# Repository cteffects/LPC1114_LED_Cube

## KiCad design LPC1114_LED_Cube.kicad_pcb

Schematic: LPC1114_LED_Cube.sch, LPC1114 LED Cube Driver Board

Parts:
AUX_I/O_0: Conn_02x08_Odd_Even; Multicomp_MC9A12-1634_2x08x2.54mm_Straight
C101, C110, C111, C114: 10uf; CP_Radial_D5.0mm_P2.50mm
C102, C104, C108, C109, C112, C113: 0.1uf; C_1206_HandSoldering
C103, C105: 22pf; C_1206_HandSoldering
C106, C107: 39pf; C_1206_HandSoldering
CH340T_0: CH340T; SSOP-20_5.3x7.2mm_Pitch0.65mm
CH340_CKO_0: Conn_01x01; Pin_Header_Straight_1x01_Pitch2.54mm
LAYER_VOUT0: Conn_01x08; Pin_Header_Straight_1x08_Pitch2.54mm
LD33V_0: LD33V; TO-220-3_Horizontal
LED_CH0, LED_CH1, LED_CH2, LED_CH3: Conn_02x08_Odd_Even; Multicomp_MC9A12-1634_2x08x2.54mm_Straight
LED_CH0_CTRL0, LED_CH1_CTRL0, LED_CH2_CTRL0, LED_CH3_CTRL0: TLC5940PWPR; TSSOP-28-1EP_4.4x9.7mm_Pitch0.65mm; MPN TLC5940PWPR; Digi-Key_PN 296-35975-1-ND
LPC1114_0: LPC1114FBD48-302; LQFP-48_7x7mm_Pitch0.5mm
MODE_SELECT_0: SW_DIP_x02; SW_DIP_x2_W7.62mm_Slide
PWR_JACK0: Barrel_Jack; BARREL_JACK
PWR_SEL1: Conn_01x03; Pin_Header_Straight_1x03_Pitch2.54mm
R101, R102, R103, R104: R; R_1206_HandSoldering
RESET0: SW_SPST; SW_Tactile_Straight_KSA0Axx1LFTR
SWDEBUG0: Conn_02x05_Odd_Even; Pin_Header_Straight_2x05_Pitch1.27mm
USB_CONN_0: USB_B
Wireless/SPI_1: Conn_02x04_Odd_Even; Pin_Header_Straight_2x04_Pitch2.54mm
XERR_CH0_BRIDGE0, XERR_CH0_BRIDGE1, XERR_CH1_BRIDGE0, XERR_CH1_BRIDGE1, XERR_CH2_BRIDGE0, XERR_CH2_BRIDGE1: Conn_01x01; Pin_Header_Straight_1x01_Pitch2.54mm
XERR_CH3_BRIDGE0: Conn_01x02; Pin_Header_Straight_1x02_Pitch2.54mm
Y101, Y102: 12MHZ; Crystal_HC49-U_Vertical

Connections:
/LayerController/LAYER_0_PWR: LAYER_VOUT0.1; also elsewhere on the board
/LayerController/LAYER_1_PWR: LAYER_VOUT0.2; also elsewhere on the board
/LayerController/LAYER_2_PWR: LAYER_VOUT0.3; also elsewhere on the board
/LayerController/LAYER_3_PWR: LAYER_VOUT0.4; also elsewhere on the board
/LayerController/LAYER_4_PWR: LAYER_VOUT0.5; also elsewhere on the board
/LayerController/LAYER_5_PWR: LAYER_VOUT0.6; also elsewhere on the board
/LayerController/LAYER_6_PWR: LAYER_VOUT0.7; also elsewhere on the board
/LayerController/LAYER_7_PWR: LAYER_VOUT0.8; also elsewhere on the board
AUX_SPI_MISO: LPC1114_0.26 (PIO2_2), Wireless/SPI_1.7
AUX_SPI_MOSI: LPC1114_0.38 (PIO2_3), Wireless/SPI_1.6
AUX_SPI_SCK: LPC1114_0.31 (PIO2_11), Wireless/SPI_1.5
AUX_SPI_SSEL: LPC1114_0.2 (PIO2_0), Wireless/SPI_1.3
BLANK: LED_CH0_CTRL0.2 (Blank), LED_CH1_CTRL0.2 (Blank), LED_CH2_CTRL0.2 (Blank), LED_CH3_CTRL0.2 (Blank), LPC1114_0.34 (PIO1_1)
DCPRG: LED_CH0_CTRL0.26 (DCPRG), LED_CH1_CTRL0.26 (DCPRG), LED_CH2_CTRL0.26 (DCPRG), LED_CH3_CTRL0.26 (DCPRG), LPC1114_0.40 (PIO1_4)
GND: AUX_I/O_0.13, AUX_I/O_0.15, AUX_I/O_0.16, C101.2, C102.2, C103.2, C104.2, C105.2, C106.2, C107.2, C108.2, C109.2, C110.2, C111.2, C112.2, C113.2, C114.2, CH340T_0.8, LD33V_0.1, LED_CH0_CTRL0.1 (GND), LED_CH0_CTRL0.29, LED_CH1_CTRL0.1 (GND), LED_CH1_CTRL0.29, LED_CH2_CTRL0.1 (GND), LED_CH2_CTRL0.29, LED_CH3_CTRL0.1 (GND), LED_CH3_CTRL0.29, LPC1114_0.5 (VSS), LPC1114_0.41 (VSS), MODE_SELECT_0.3, MODE_SELECT_0.4, PWR_JACK0.2, R101.1, R102.1, R103.1, R104.1, RESET0.2, SWDEBUG0.3, SWDEBUG0.5, SWDEBUG0.9, USB_CONN_0.4, USB_CONN_0.5, Wireless/SPI_1.1; also elsewhere on the board
INPUT_MODE_SELECT: AUX_I/O_0.5, LPC1114_0.10 (PIO0_2), MODE_SELECT_0.2
ISP_ENTRY: LPC1114_0.4 (PIO0_1), MODE_SELECT_0.1
LAYER_0_ON: LPC1114_0.19 (PIO2_4); also elsewhere on the board
LAYER_1_ON: LPC1114_0.20 (PIO2_5); also elsewhere on the board
LAYER_2_ON: LPC1114_0.1 (PIO2_6); also elsewhere on the board
LAYER_3_ON: LPC1114_0.11 (PIO2_7); also elsewhere on the board
LAYER_4_ON: LPC1114_0.12 (PIO2_8); also elsewhere on the board
LAYER_5_ON: LPC1114_0.24 (PIO2_9); also elsewhere on the board
LAYER_6_ON: LPC1114_0.25 (PIO2_10); also elsewhere on the board
LAYER_7_ON: LPC1114_0.13 (PIO2_1); also elsewhere on the board
LED_CH0_0: LED_CH0.15, LED_CH0_CTRL0.7 (OUT0)
LED_CH0_1: LED_CH0.13, LED_CH0_CTRL0.8 (OUT1)
LED_CH0_2: LED_CH0.11, LED_CH0_CTRL0.9 (OUT2)
LED_CH0_3: LED_CH0.9, LED_CH0_CTRL0.10 (OUT3)
LED_CH0_4: LED_CH0.7, LED_CH0_CTRL0.11 (OUT4)
LED_CH0_5: LED_CH0.5, LED_CH0_CTRL0.12 (OUT5)
LED_CH0_6: LED_CH0.3, LED_CH0_CTRL0.13 (OUT6)
LED_CH0_7: LED_CH0.1, LED_CH0_CTRL0.14 (OUT7)
LED_CH0_8: LED_CH0.2, LED_CH0_CTRL0.15 (OUT8)
LED_CH0_9: LED_CH0.4, LED_CH0_CTRL0.16 (OUT9)
LED_CH0_10: LED_CH0.6, LED_CH0_CTRL0.17 (OUT10)
LED_CH0_11: LED_CH0.8, LED_CH0_CTRL0.18 (OUT11)
LED_CH0_12: LED_CH0.10, LED_CH0_CTRL0.19 (OUT12)
LED_CH0_13: LED_CH0.12, LED_CH0_CTRL0.20 (OUT13)
LED_CH0_14: LED_CH0.14, LED_CH0_CTRL0.21 (OUT14)
LED_CH0_15: LED_CH0.16, LED_CH0_CTRL0.22 (OUT15)
LED_CH1_0: LED_CH1.15, LED_CH1_CTRL0.7 (OUT0)
LED_CH1_1: LED_CH1.13, LED_CH1_CTRL0.8 (OUT1)
LED_CH1_2: LED_CH1.11, LED_CH1_CTRL0.9 (OUT2)
LED_CH1_3: LED_CH1.9, LED_CH1_CTRL0.10 (OUT3)
LED_CH1_4: LED_CH1.7, LED_CH1_CTRL0.11 (OUT4)
LED_CH1_5: LED_CH1.5, LED_CH1_CTRL0.12 (OUT5)
LED_CH1_6: LED_CH1.3, LED_CH1_CTRL0.13 (OUT6)
LED_CH1_7: LED_CH1.1, LED_CH1_CTRL0.14 (OUT7)
LED_CH1_8: LED_CH1.2, LED_CH1_CTRL0.15 (OUT8)
LED_CH1_9: LED_CH1.4, LED_CH1_CTRL0.16 (OUT9)
LED_CH1_10: LED_CH1.6, LED_CH1_CTRL0.17 (OUT10)
LED_CH1_11: LED_CH1.8, LED_CH1_CTRL0.18 (OUT11)
LED_CH1_12: LED_CH1.10, LED_CH1_CTRL0.19 (OUT12)
LED_CH1_13: LED_CH1.12, LED_CH1_CTRL0.20 (OUT13)
LED_CH1_14: LED_CH1.14, LED_CH1_CTRL0.21 (OUT14)
LED_CH1_15: LED_CH1.16, LED_CH1_CTRL0.22 (OUT15)
LED_CH2_0: LED_CH2.15, LED_CH2_CTRL0.7 (OUT0)
LED_CH2_1: LED_CH2.13, LED_CH2_CTRL0.8 (OUT1)
LED_CH2_2: LED_CH2.11, LED_CH2_CTRL0.9 (OUT2)
LED_CH2_3: LED_CH2.9, LED_CH2_CTRL0.10 (OUT3)
LED_CH2_4: LED_CH2.7, LED_CH2_CTRL0.11 (OUT4)
LED_CH2_5: LED_CH2.5, LED_CH2_CTRL0.12 (OUT5)
LED_CH2_6: LED_CH2.3, LED_CH2_CTRL0.13 (OUT6)
LED_CH2_7: LED_CH2.1, LED_CH2_CTRL0.14 (OUT7)
LED_CH2_8: LED_CH2.2, LED_CH2_CTRL0.15 (OUT8)
LED_CH2_9: LED_CH2.4, LED_CH2_CTRL0.16 (OUT9)
LED_CH2_10: LED_CH2.6, LED_CH2_CTRL0.17 (OUT10)
LED_CH2_11: LED_CH2.8, LED_CH2_CTRL0.18 (OUT11)
LED_CH2_12: LED_CH2.10, LED_CH2_CTRL0.19 (OUT12)
LED_CH2_13: LED_CH2.12, LED_CH2_CTRL0.20 (OUT13)
LED_CH2_14: LED_CH2.14, LED_CH2_CTRL0.21 (OUT14)
LED_CH2_15: LED_CH2.16, LED_CH2_CTRL0.22 (OUT15)
LED_CH3_0: LED_CH3.15, LED_CH3_CTRL0.7 (OUT0)
LED_CH3_1: LED_CH3.13, LED_CH3_CTRL0.8 (OUT1)
LED_CH3_2: LED_CH3.11, LED_CH3_CTRL0.9 (OUT2)
LED_CH3_3: LED_CH3.9, LED_CH3_CTRL0.10 (OUT3)
LED_CH3_4: LED_CH3.7, LED_CH3_CTRL0.11 (OUT4)
LED_CH3_5: LED_CH3.5, LED_CH3_CTRL0.12 (OUT5)
LED_CH3_6: LED_CH3.3, LED_CH3_CTRL0.13 (OUT6)
LED_CH3_7: LED_CH3.1, LED_CH3_CTRL0.14 (OUT7)
LED_CH3_8: LED_CH3.2, LED_CH3_CTRL0.15 (OUT8)
LED_CH3_9: LED_CH3.4, LED_CH3_CTRL0.16 (OUT9)
LED_CH3_10: LED_CH3.6, LED_CH3_CTRL0.17 (OUT10)
LED_CH3_11: LED_CH3.8, LED_CH3_CTRL0.18 (OUT11)
LED_CH3_12: LED_CH3.10, LED_CH3_CTRL0.19 (OUT12)
LED_CH3_13: LED_CH3.12, LED_CH3_CTRL0.20 (OUT13)
LED_CH3_14: LED_CH3.14, LED_CH3_CTRL0.21 (OUT14)
LED_CH3_15: LED_CH3.16, LED_CH3_CTRL0.22 (OUT15)
LED_DATA_SCK: LED_CH0_CTRL0.4 (SCLK), LED_CH1_CTRL0.4 (SCLK), LED_CH2_CTRL0.4 (SCLK), LED_CH3_CTRL0.4 (SCLK), LPC1114_0.22 (PIO0_6)
LED_GS_CLK: LED_CH0_CTRL0.25 (GSCLK), LED_CH1_CTRL0.25 (GSCLK), LED_CH2_CTRL0.25 (GSCLK), LED_CH3_CTRL0.25 (GSCLK), LPC1114_0.32 (PIO0_11)
LED_SIN: LED_CH0_CTRL0.5 (SIN), LPC1114_0.28 (PIO0_9)
unnamed: C103.1, CH340T_0.9, Y101.1
unnamed: C105.1, CH340T_0.10, Y101.2
unnamed: C106.1, LPC1114_0.7 (XTALOUT), Y102.1
unnamed: C107.1, LPC1114_0.6 (XTALIN), Y102.2
unnamed: CH340T_0.1, CH340_CKO_0.1
unnamed: CH340T_0.6, USB_CONN_0.3
unnamed: CH340T_0.7, USB_CONN_0.2
unnamed: LED_CH0_CTRL0.27 (IREF), R102.2
unnamed: LED_CH1_CTRL0.27 (IREF), R101.2
unnamed: LED_CH2_CTRL0.27 (IREF), R104.2
unnamed: LED_CH3_CTRL0.27 (IREF), R103.2
PIO0_3: AUX_I/O_0.7, LPC1114_0.14 (PIO0_3)
PIO0_4: AUX_I/O_0.9, LPC1114_0.15 (PIO0_4)
PIO0_5: AUX_I/O_0.11, LPC1114_0.16 (PIO0_5)
PIO1_5: AUX_I/O_0.6, LPC1114_0.45 (PIO1_5)
PIO1_10: AUX_I/O_0.8, LPC1114_0.30 (PIO1_10)
PIO1_11: AUX_I/O_0.10, LPC1114_0.42 (PIO1_11)
PIO3_4: AUX_I/O_0.12, LPC1114_0.18 (PIO3_4)
PIO3_5: AUX_I/O_0.14, LPC1114_0.21 (PIO3_5)
RXD_USB: CH340T_0.4, LPC1114_0.47 (PIO1_7)
SOUT_CH0_CH1: LED_CH0_CTRL0.24 (SOUT), LED_CH1_CTRL0.5 (SIN)
SOUT_CH1_CH2: LED_CH1_CTRL0.24 (SOUT), LED_CH2_CTRL0.5 (SIN)
SOUT_CH2_CH3: LED_CH2_CTRL0.24 (SOUT), LED_CH3_CTRL0.5 (SIN)
SWCLK: LPC1114_0.29 (PIO0_10), SWDEBUG0.4
SWDIO: LPC1114_0.39 (PIO1_3), SWDEBUG0.2
TXD_USB: CH340T_0.3, LPC1114_0.46 (PIO1_6)
V3: AUX_I/O_0.1, AUX_I/O_0.2, AUX_I/O_0.3, AUX_I/O_0.4, C101.1, C102.1, C104.1, C108.1, C109.1, C111.1, C112.1, C113.1, C114.1, CH340T_0.5, CH340T_0.19, LD33V_0.2, LED_CH0_CTRL0.28 (VCC), LED_CH1_CTRL0.28 (VCC), LED_CH2_CTRL0.28 (VCC), LED_CH3_CTRL0.28 (VCC), LPC1114_0.8 (VDD), LPC1114_0.44 (VDD), SWDEBUG0.1, Wireless/SPI_1.2
V5: PWR_SEL1.2; also elsewhere on the board
V5_AUX: PWR_JACK0.1, PWR_SEL1.3
V5_USB: C110.1, LD33V_0.3, PWR_SEL1.1, USB_CONN_0.1
VPRG: LED_CH0_CTRL0.6 (VPRG), LED_CH1_CTRL0.6 (VPRG), LED_CH2_CTRL0.6 (VPRG), LED_CH3_CTRL0.6 (VPRG), LPC1114_0.35 (PIO1_2)
WIRELESS_CSN: LPC1114_0.9 (PIO1_8), Wireless/SPI_1.4
WIRELESS_IRQ: LPC1114_0.17 (PIO1_9), Wireless/SPI_1.8
XERR_CH0: LED_CH0_CTRL0.23 (XERR), XERR_CH0_BRIDGE0.1
XERR_CH1: LED_CH1_CTRL0.23 (XERR), XERR_CH1_BRIDGE0.1
XERR_CH2: LED_CH2_CTRL0.23 (XERR), XERR_CH2_BRIDGE0.1
XERR_CH3: LED_CH3_CTRL0.23 (XERR), XERR_CH3_BRIDGE0.1
XERR_MCU_CH0: LPC1114_0.36 (PIO3_0), XERR_CH0_BRIDGE1.1
XERR_MCU_CH1: LPC1114_0.37 (PIO3_1), XERR_CH1_BRIDGE1.1
XERR_MCU_CH2: LPC1114_0.43 (PIO3_2), XERR_CH2_BRIDGE1.1
XERR_MCU_CH3: LPC1114_0.48 (PIO3_3), XERR_CH3_BRIDGE0.2
XLAT: LED_CH0_CTRL0.3 (XLAT), LED_CH1_CTRL0.3 (XLAT), LED_CH2_CTRL0.3 (XLAT), LED_CH3_CTRL0.3 (XLAT), LPC1114_0.33 (PIO1_0)
_CTS_MCU: CH340T_0.16, LPC1114_0.23 (PIO0_7)
_RESET: LPC1114_0.3 (PIO0_0), RESET0.1, SWDEBUG0.10
_RTS_MCU: CH340T_0.11, LPC1114_0.27 (PIO0_8)

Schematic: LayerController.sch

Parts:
Q201, Q202, Q203, Q204, Q209, Q210, Q211, Q212: BSS138; SOT-23; MPN BSS138; Digi-Key_PN BSS138CT-ND
Q205, Q206, Q207, Q208, Q213, Q214, Q215, Q216: IRLML6402TRPBF; SOT-23; MPN IRLML6402TRPBF; Digi-Key_PN IRLML6402PBFCT-ND
R201, R202, R203, R204, R205, R206, R207, R208: 1K; R_1206_HandSoldering
R209, R210, R211, R212, R213, R214, R215, R216: 100K; R_1206_HandSoldering
R217, R218, R219, R220, R221, R222, R223, R224: 100R; R_1206_HandSoldering

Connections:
/LayerController/LAYER_0_PWR: Q205.3; also elsewhere on the board
/LayerController/LAYER_1_PWR: Q206.3; also elsewhere on the board
/LayerController/LAYER_2_PWR: Q207.3; also elsewhere on the board
/LayerController/LAYER_3_PWR: Q208.3; also elsewhere on the board
/LayerController/LAYER_4_PWR: Q213.3; also elsewhere on the board
/LayerController/LAYER_5_PWR: Q214.3; also elsewhere on the board
/LayerController/LAYER_6_PWR: Q215.3; also elsewhere on the board
/LayerController/LAYER_7_PWR: Q216.3; also elsewhere on the board
GND: Q201.2, Q202.2, Q203.2, Q204.2, Q209.2, Q210.2, Q211.2, Q212.2, R209.2, R210.2, R211.2, R212.2, R213.2, R214.2, R215.2, R216.2; also elsewhere on the board
LAYER_0_ON: R217.2; also elsewhere on the board
LAYER_1_ON: R218.2; also elsewhere on the board
LAYER_2_ON: R219.2; also elsewhere on the board
LAYER_3_ON: R220.2; also elsewhere on the board
LAYER_4_ON: R221.2; also elsewhere on the board
LAYER_5_ON: R222.2; also elsewhere on the board
LAYER_6_ON: R223.2; also elsewhere on the board
LAYER_7_ON: R224.2; also elsewhere on the board
unnamed: Q201.1, R209.1, R217.1
unnamed: Q201.3, Q205.1, R201.2
unnamed: Q202.1, R210.1, R218.1
unnamed: Q202.3, Q206.1, R202.2
unnamed: Q203.1, R211.1, R219.1
unnamed: Q203.3, Q207.1, R203.2
unnamed: Q204.1, R212.1, R220.1
unnamed: Q204.3, Q208.1, R204.2
unnamed: Q209.1, R213.1, R221.1
unnamed: Q209.3, Q213.1, R205.2
unnamed: Q210.1, R214.1, R222.1
unnamed: Q210.3, Q214.1, R206.2
unnamed: Q211.1, R215.1, R223.1
unnamed: Q211.3, Q215.1, R207.2
unnamed: Q212.1, R216.1, R224.1
unnamed: Q212.3, Q216.1, R208.2
V5: Q205.2, Q206.2, Q207.2, Q208.2, Q213.2, Q214.2, Q215.2, Q216.2, R201.1, R202.1, R203.1, R204.1, R205.1, R206.1, R207.1, R208.1; also elsewhere on the board

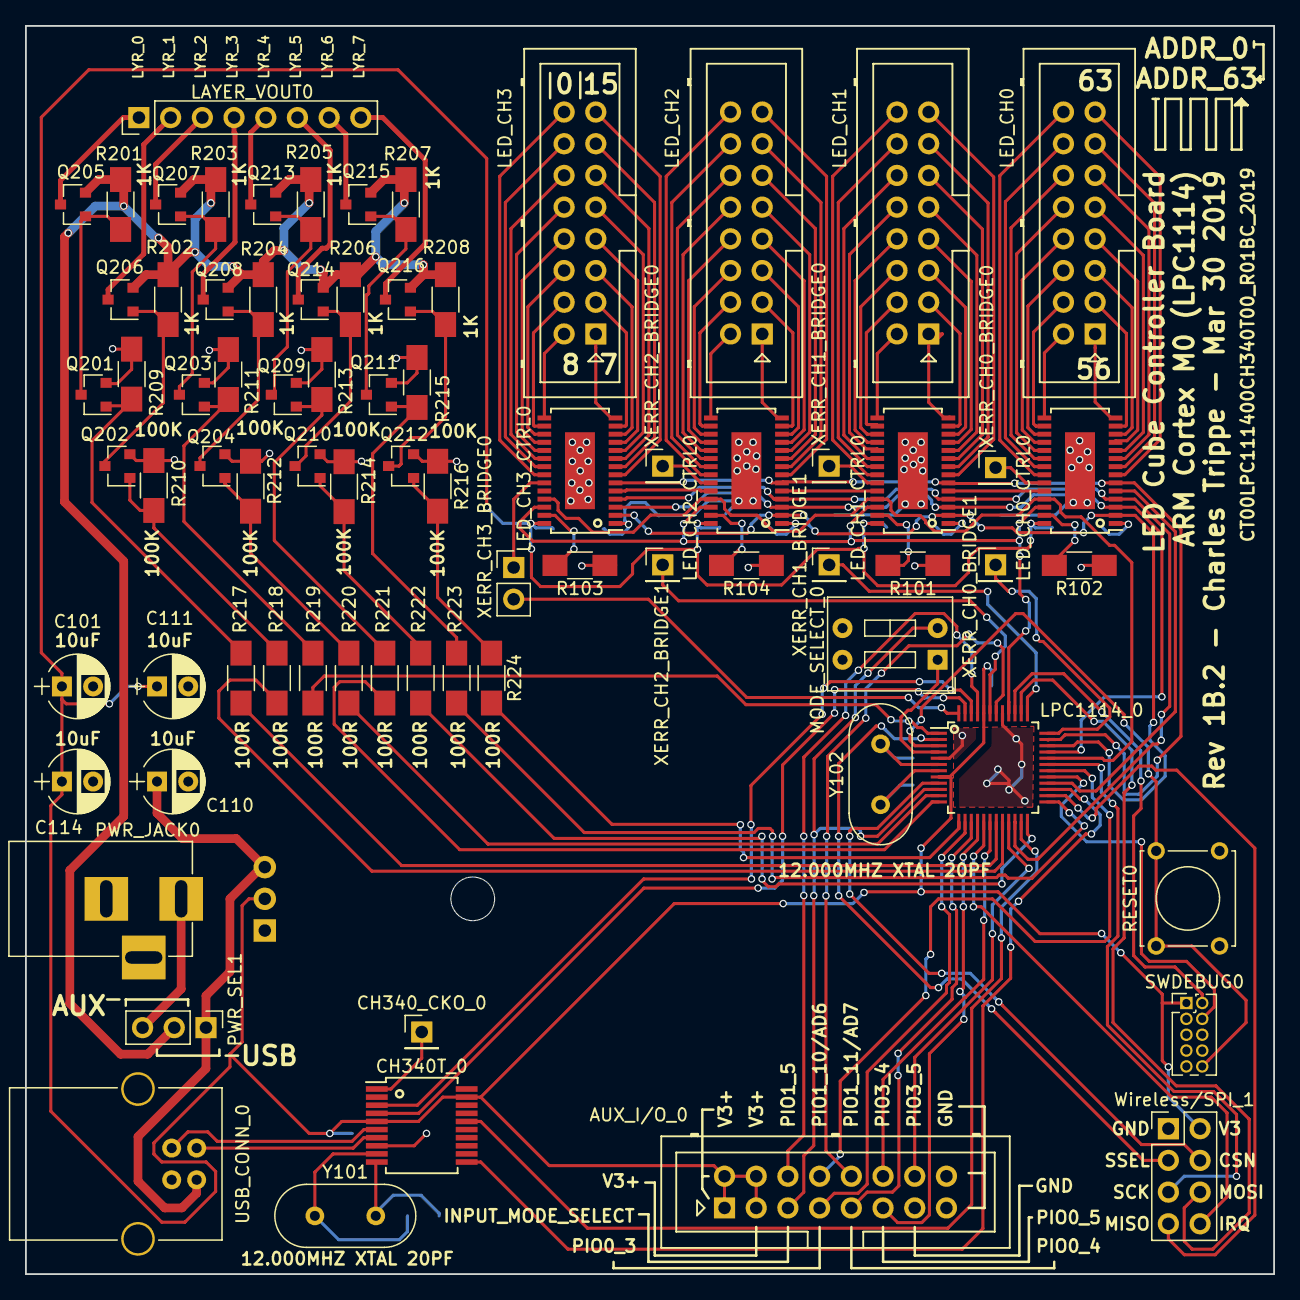
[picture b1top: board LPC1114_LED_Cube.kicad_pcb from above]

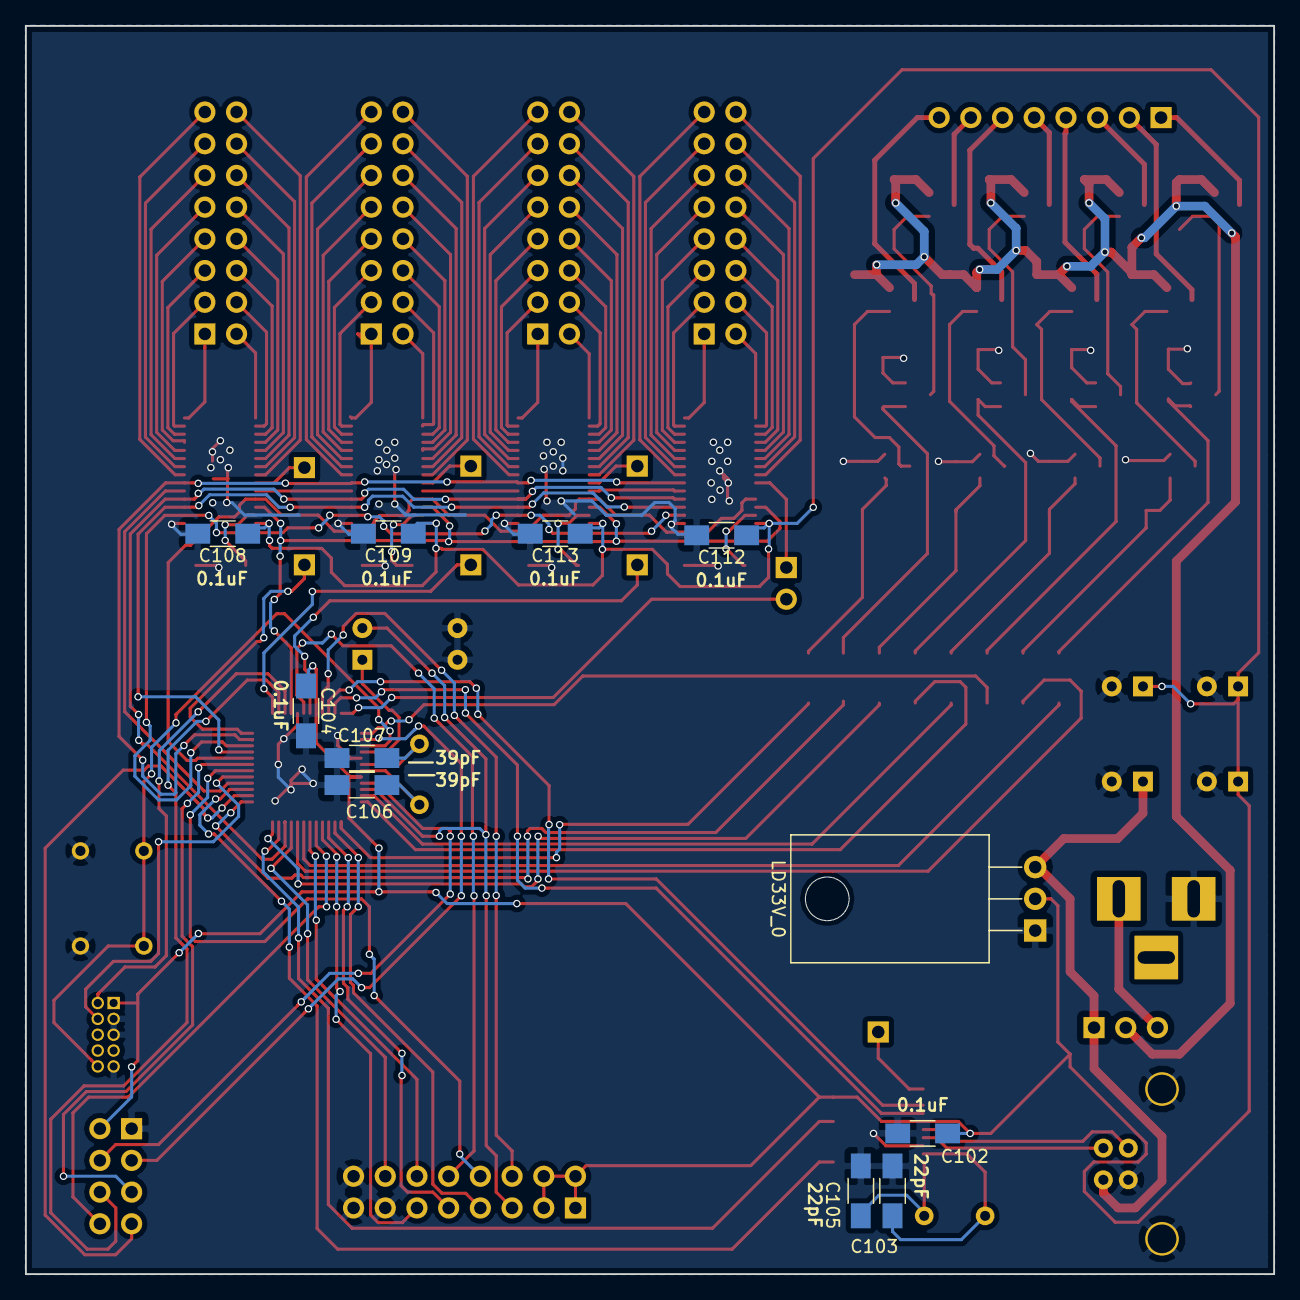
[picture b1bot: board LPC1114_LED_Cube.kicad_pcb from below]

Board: 2 copper layers, 100.0 x 100.0 mm, 88 parts (11 on the bottom side), 153 nets.

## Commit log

2018-06-16 :confetti_ball: Added .gitattributes & .gitignore files
2018-06-24 Created CH340T library and added to schematic
2018-06-25 added USB-to-Serial bridge hardware added ld33v 3.3v voltage regulator
2018-06-25 added KiCad cache and backups to ignore
2018-06-25 Removing ignored files
2018-06-28 Added power and debug circuitry Started layer controller
2018-06-29 Added AUX_SPI + Wireless Module Port Rearranged pins
2018-07-03 Finalized Schematic for Rev. A1
2018-07-05 Initial PCB layout and some tracks Ingored more backup file types
2018-07-05 More pcb layout
2018-07-08 redo layout for EMC
2018-07-09 Fixed some schematic bugs. Added input mode switch.
2018-07-23 improved initial layout for better EMC and compactness Upgraded to KiCad 5.0
2018-07-23 more layout
2018-07-30 Finished Rev 1A Layout
2018-07-30 Completed Rev 1A
2018-10-28 Rev 1B: Corrected silkscreen component values
2018-10-28 fixed corrupted schematic file
2018-10-28 corrected some labeling
2018-10-30 Text alignment
2018-11-18 changed some pinouts Added hardware flow control lines between MCU and serial IC
2018-11-18 updated gerbers to new pcb revision
2019-03-30 added tent on vias
2019-03-31 added orientation markers to ICs
